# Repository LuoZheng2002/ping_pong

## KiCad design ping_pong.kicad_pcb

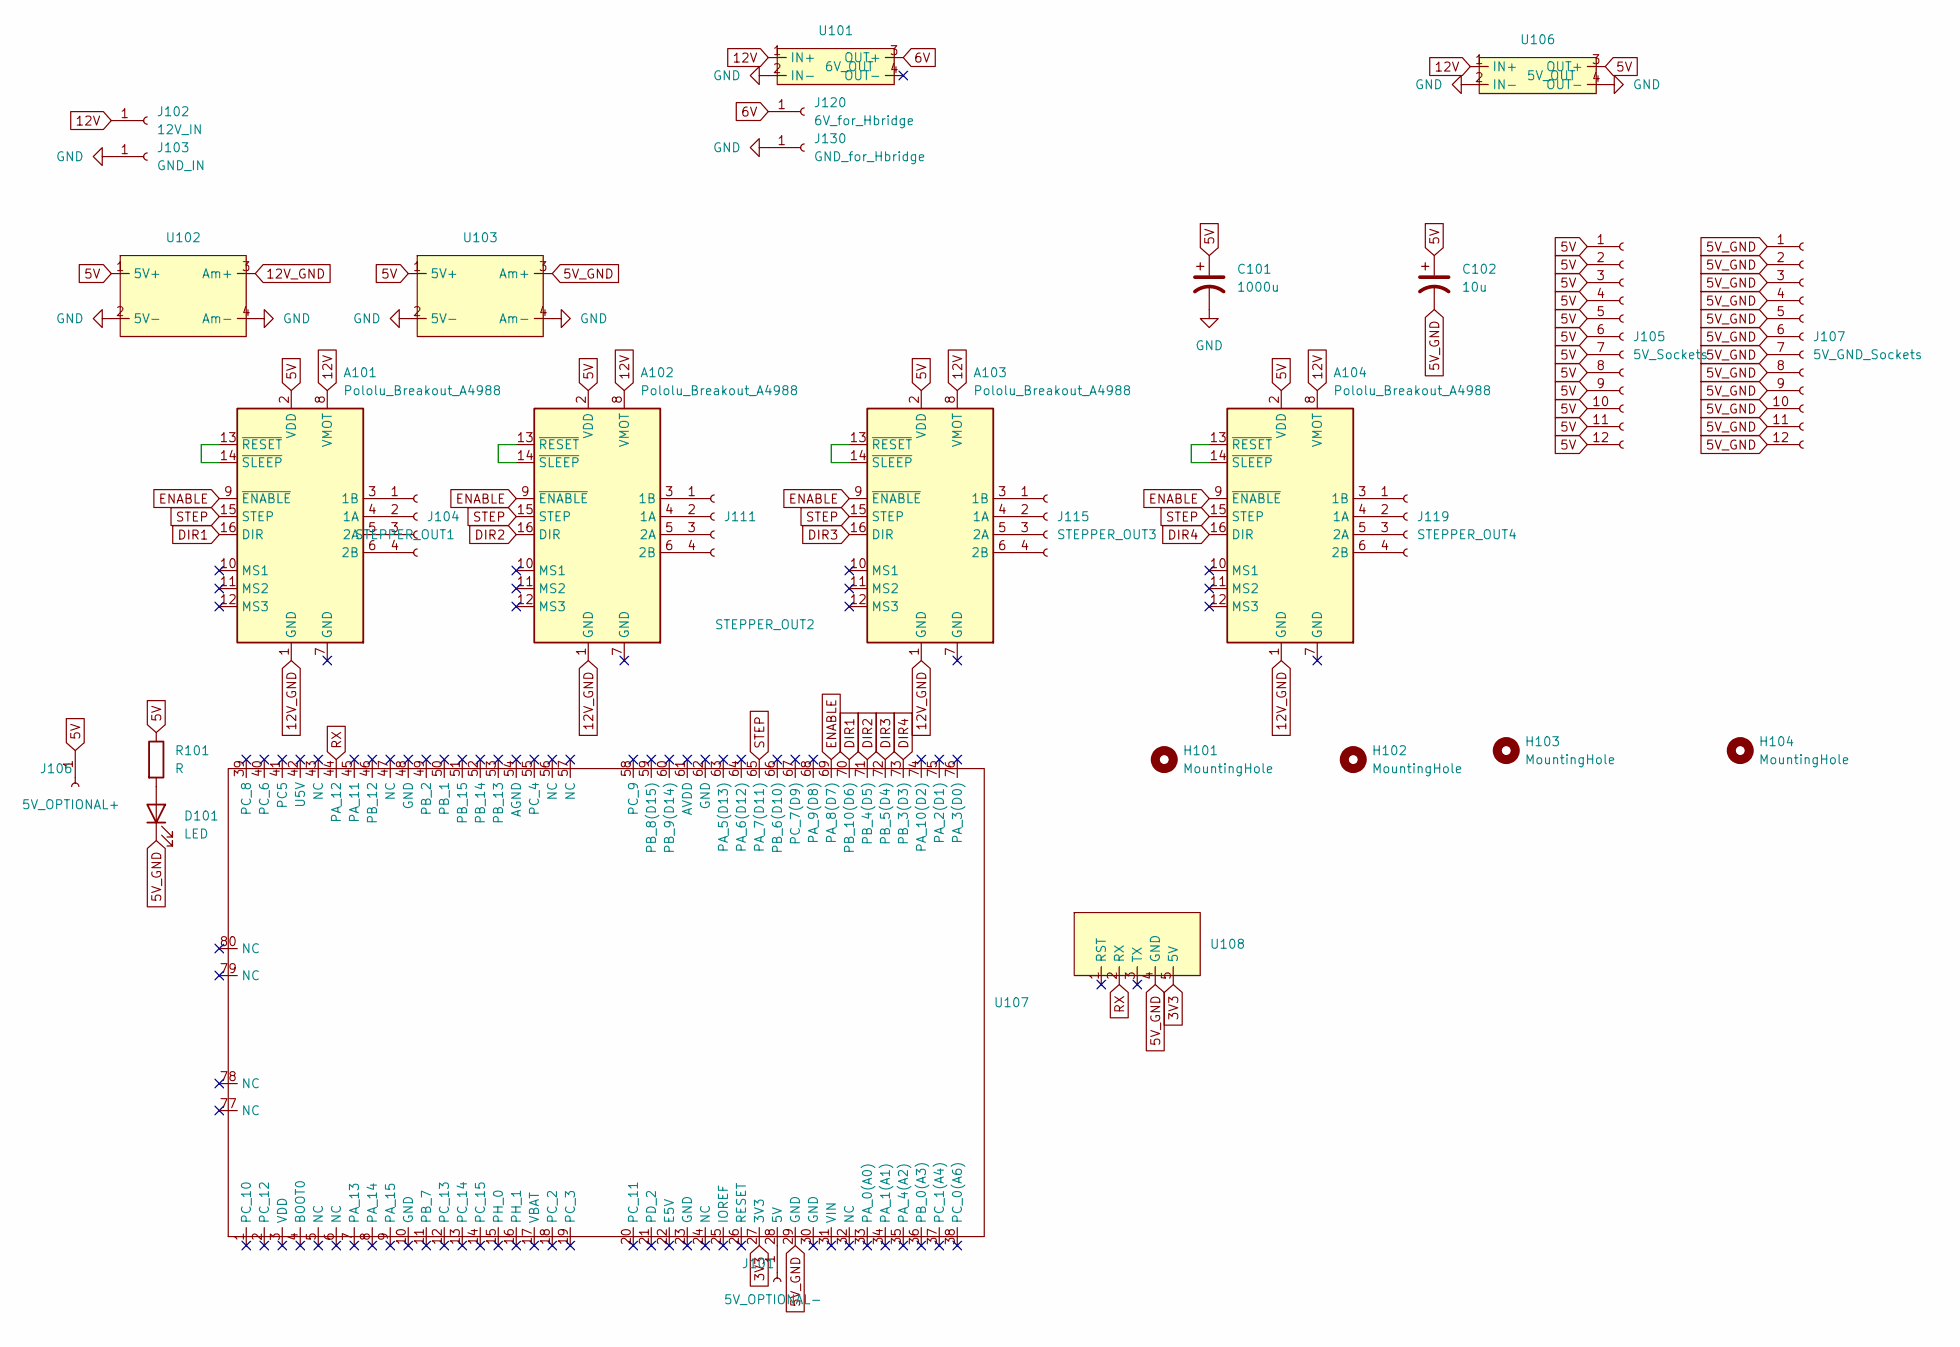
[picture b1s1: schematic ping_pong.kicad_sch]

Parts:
A101, A102, A103, A104: Pololu_Breakout_A4988; Pololu_Breakout-16_15.2x20.3mm
C101: 1000u; CP_Radial_D10.0mm_P5.00mm
C102: 10u; CP_Radial_D5.0mm_P2.50mm
D101: LED; LED_D5.0mm
H101, H102, H103, H104: MountingHole; MountingHole_3.2mm_M3
J101: 5V_OPTIONAL-; MyPinSocket
J102: 12V_IN; MyPinSocket
J103: GND_IN; MyPinSocket
J104: STEPPER_OUT1; PinSocket_1x04_P2.54mm_Vertical
J105: 5V_Sockets; PinSocket_1x12_P2.54mm_Vertical
J106: 5V_OPTIONAL+; MyPinSocket
J107: 5V_GND_Sockets; PinSocket_1x12_P2.54mm_Vertical
J111: STEPPER_OUT2; PinSocket_1x04_P2.54mm_Vertical
J115: STEPPER_OUT3; PinSocket_1x04_P2.54mm_Vertical
J119: STEPPER_OUT4; PinSocket_1x04_P2.54mm_Vertical
J120: 6V_for_Hbridge; MyPinSocket
J130: GND_for_Hbridge; MyPinSocket
R101: R; My7.62mmResistor
U101: 6V_OUT; LM2596
U102, U103: Ammeter
U106: 5V_OUT; LM2596
U107: NUCLEO-F401RE
U108: XBEE

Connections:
3V3: U107.27 (3V3), U108.5 (5V)
5V: A101.2 (VDD), A102.2 (VDD), A103.2 (VDD), A104.2 (VDD), C101.1, C102.1, J105.1, J105.2, J105.3, J105.4, J105.5, J105.6, J105.7, J105.8, J105.9, J105.10, J105.11, J105.12, J106.1, R101.1, U102.1 (5V+), U103.1 (5V+), U106.3 (OUT+)
5V_GND: C102.2, D101.1 (K), J107.1, J107.2, J107.3, J107.4, J107.5, J107.6, J107.7, J107.8, J107.9, J107.10, J107.11, J107.12, U103.3 (Am+), U107.29 (GND), U108.4 (GND)
6V: J120.1, U101.3 (OUT+)
12V: A101.8 (VMOT), A102.8 (VMOT), A103.8 (VMOT), A104.8 (VMOT), J102.1, U101.1 (IN+), U106.1 (IN+)
12V_GND: A101.1 (GND), A102.1 (GND), A103.1 (GND), A104.1 (GND), U102.3 (Am+)
DIR1: A101.16 (DIR), U107.70 (PB_10(D6))
DIR2: A102.16 (DIR), U107.71 (PB_4(D5))
DIR3: A103.16 (DIR), U107.72 (PB_5(D4))
DIR4: A104.16 (DIR), U107.73 (PB_3(D3))
ENABLE: A101.9 (~ENABLE), A102.9 (~ENABLE), A103.9 (~ENABLE), A104.9 (~ENABLE), U107.69 (PA_8(D7))
GND: C101.2, J103.1, J130.1, U101.2 (IN-), U102.2 (5V-), U102.4 (Am-), U103.2 (5V-), U103.4 (Am-), U106.2 (IN-), U106.4 (OUT-)
unnamed: A101.4 (1A), J104.2
unnamed: A101.3 (1B), J104.1
unnamed: A101.5 (2A), J104.3
unnamed: A101.6 (2B), J104.4
unnamed: A101.13 (~RESET), A101.14 (~SLEEP)
unnamed: A102.4 (1A), J111.2
unnamed: A102.3 (1B), J111.1
unnamed: A102.5 (2A), J111.3
unnamed: A102.6 (2B), J111.4
unnamed: A102.13 (~RESET), A102.14 (~SLEEP)
unnamed: A103.4 (1A), J115.2
unnamed: A103.3 (1B), J115.1
unnamed: A103.5 (2A), J115.3
unnamed: A103.6 (2B), J115.4
unnamed: A103.13 (~RESET), A103.14 (~SLEEP)
unnamed: A104.4 (1A), J119.2
unnamed: A104.3 (1B), J119.1
unnamed: A104.5 (2A), J119.3
unnamed: A104.6 (2B), J119.4
unnamed: A104.13 (~RESET), A104.14 (~SLEEP)
unnamed: D101.2 (A), R101.2
unnamed: J101.1, U107.28 (5V)
RX: U107.44 (PA_12), U108.2 (RX)
STEP: A101.15 (STEP), A102.15 (STEP), A103.15 (STEP), A104.15 (STEP), U107.65 (PA_7(D11))

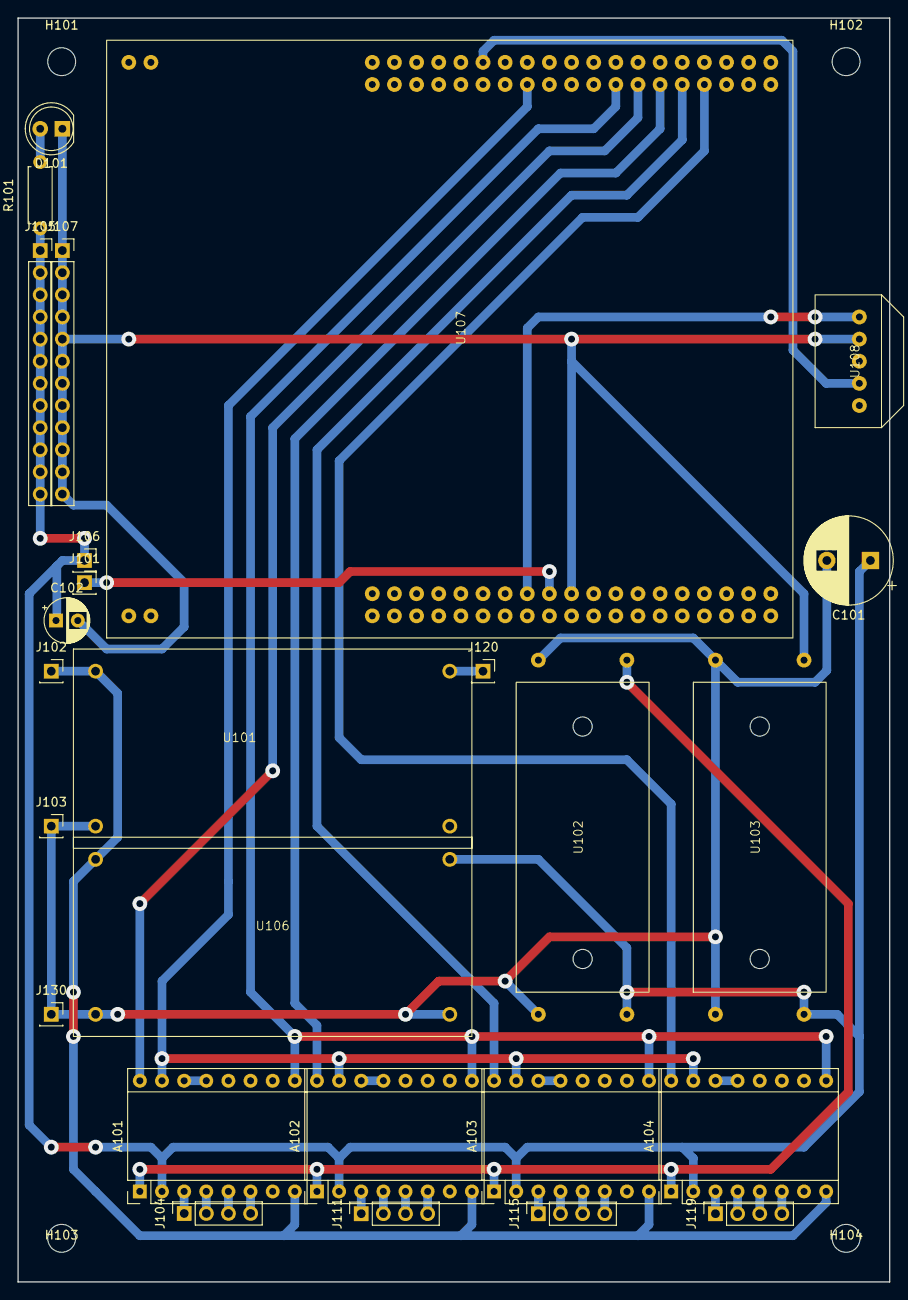
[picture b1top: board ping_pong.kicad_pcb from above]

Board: 2 copper layers, 100.0 x 145.0 mm, 30 parts (0 on the bottom side), 36 nets.

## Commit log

2024-04-10 checkpoint
